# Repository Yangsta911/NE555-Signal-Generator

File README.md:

# NE555-Signal-Generator
Using a NE555 chip to create a square wave signal generator

# Prerequisites
- Copper clad board
- Schematic drawing cad software e.g. KiCad
- Toner transfer paper
- Hydrogen peroxide
- Hydrochloric acid
- Soldering iron
- Clothes iron
- Sticky tape
- Vice
- Plastic tweezers
- Drill press
- 3 10nf Capacitors
- 2 Leds
- 2 variable resistors
- 2 230 ohm resistor
- 1k ohm resistor
- DC barrel power jack

# To build
## Etching process.
1. Use the schematics file NE555 Signal Generator new.kicad_pcb.

Pcb board diagram
2. Print the pcb board design onto toner transfer paper.
3. Cut out the printed pcb design outline.
4. Prepare an appropriate sized copper clad board for the circuit to go onto.
5. Roughly sand the copper board to ensure that the copper is clean to allow for bettter toner transfer.
6. Use sticky tape to attatch the toner paper onto the pcb board. Ensure that the paper is flat and in contact with the copper board.
7. Place clothes iron onto Vice clamp to ensure the heated side is facing up.
8. Preheat the clothes iron to silk setting.
9. Once hot place the copper board onto the iron and apply force evenly onto the board. Continue to do so for 15-20 minutes.
10. Remove the coppper board and allow it to cool.
11. Once cool place the copper board into cold water and carefully peel off the toner transfer paper.

Toner transfer result
12. Inspect the board and see if the proper circuitry has been transfered. If the result is poor the board can be sanded and the process can be repeated. Minor imperfections can be filled in with paint instead.
13. If the transfer is satisfacory then the etching process can begin.
14. Measure out 25ml of hydrochloric acid and 50ml of hydrogen peroxide.
15. Add the hydrochloric acid into the hydrogen peroxide slowly to form the etching solution.

etching solution
16. Carefully place the copper board into the solution using plastic tweezers.

etching solution
17. Stir the solution constantly and observe the board to see if the corrision has taken place. The process should take around 15-20mins.
18. Once the board has corroded carefully remove the board from the solution using plastic tweezers and rinse with clear water.
19. Sand off the excess paint and print that remains on the board and the etching should be finished.

Etched board before sanding

Front of final pcb board

Back of pcb board

## Finish the circuitry of the board.
 1. Drill holes into the board using a drill press for the legs of the components.
 2. Using the schematic Resistors R1, R5 are 230 ohm resistors. Capacitors, C1, C2, C3 are 1nf capacitors.

Schematic of circuit
 3. Solder all of the components onto the board according to the schematic.
 
 Front of the final pcb board
 
 Back of the final pcb board

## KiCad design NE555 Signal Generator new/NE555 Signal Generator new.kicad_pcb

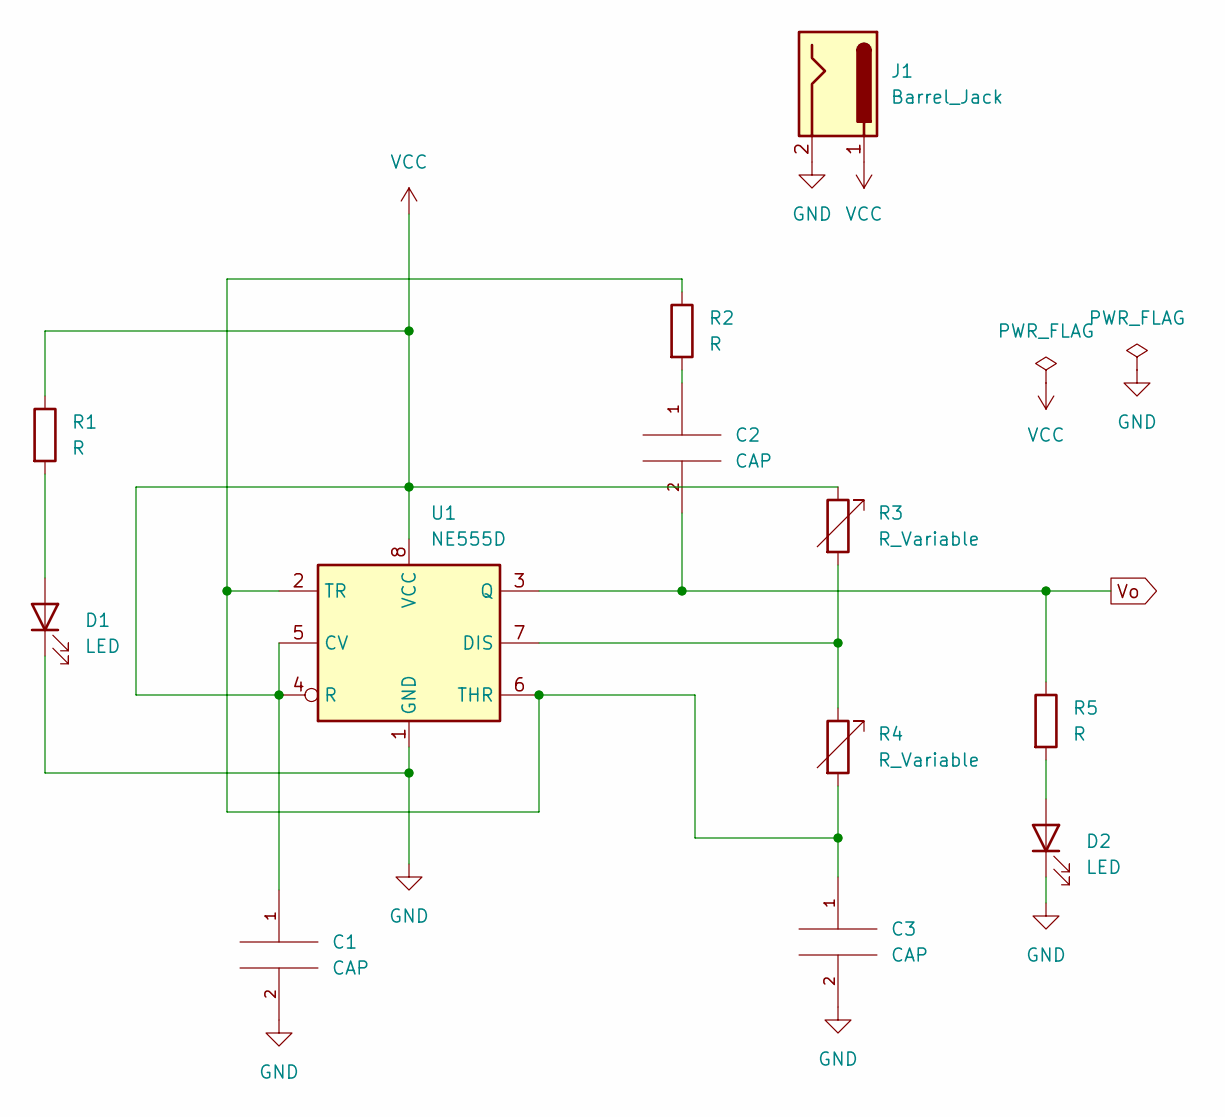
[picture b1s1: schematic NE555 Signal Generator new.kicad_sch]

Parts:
C1, C2, C3: CAP; C_Disc_D3.8mm_W2.6mm_P2.50mm
D1, D2: LED; LED_D1.8mm_W3.3mm_H2.4mm
J1: Barrel_Jack; BarrelJack_Horizontal
R1, R2, R5: R; R_Axial_DIN0207_L6.3mm_D2.5mm_P7.62mm_Horizontal
R3, R4: R_Variable; Potentiometer_Omeg_PC16BU_Vertical
U1: NE555D; SOIC-8_3.9x4.9mm_P1.27mm

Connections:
GND: C1.2, C3.2, D1.1 (K), D2.1 (K), J1.2, U1.1 (GND)
unnamed: C2.1, R2.2
unnamed: C3.1, R2.1, R4.2, U1.2 (TR), U1.6 (THR)
unnamed: D1.2 (A), R1.2
unnamed: D2.2 (A), R5.2
unnamed: R3.2, R4.1, U1.7 (DIS)
VCC: C1.1, J1.1, R1.1, R3.1, U1.4 (R), U1.5 (CV), U1.8 (VCC)
Vo: C2.2, R5.1, U1.3 (Q)

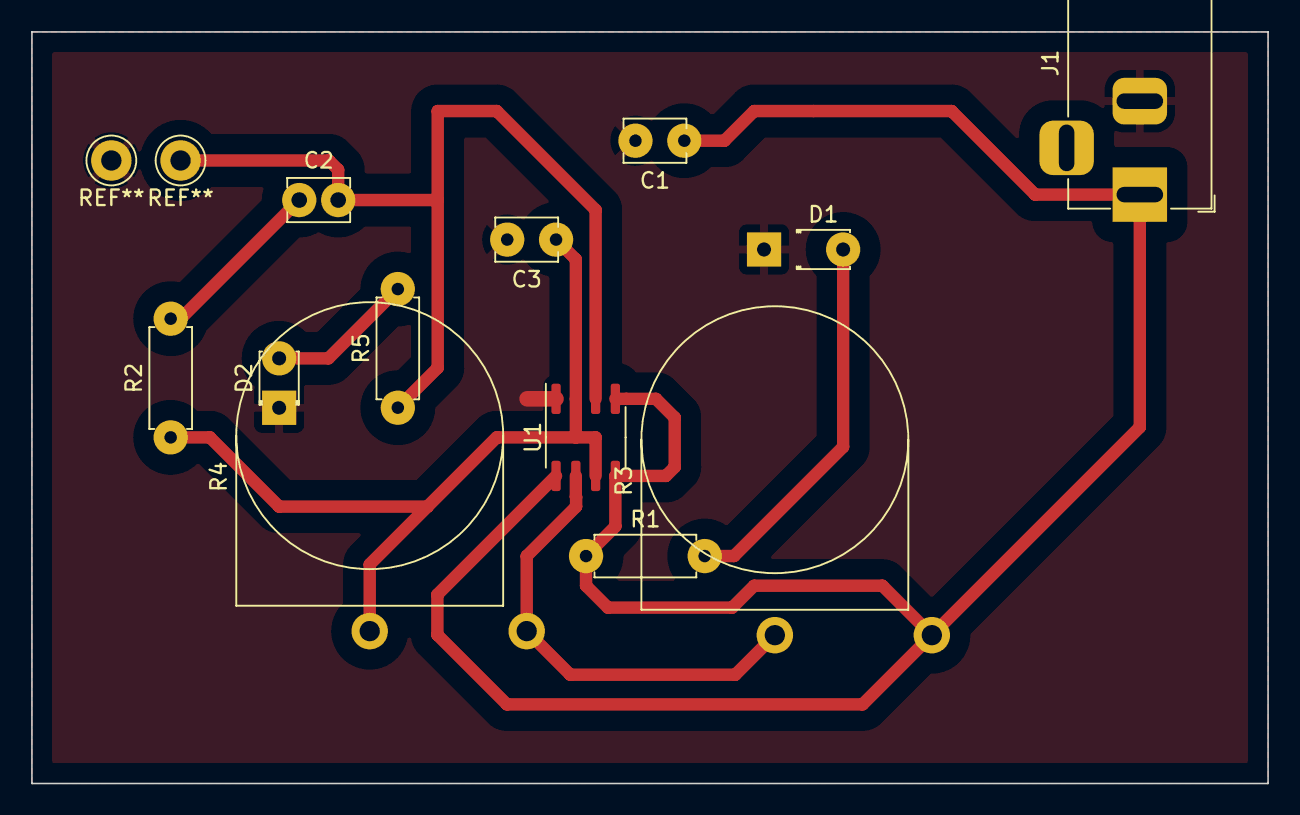
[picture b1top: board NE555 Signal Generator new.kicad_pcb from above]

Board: 2 copper layers, 79.4 x 48.3 mm, 12 parts (0 on the bottom side), 8 nets.
